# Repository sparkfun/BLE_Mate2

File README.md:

SparkFun BLE Mate 2
========================================

[*SparkFun BLE Mate 2 (WRL-13019)*](https://www.sparkfun.com/products/13019)

Repository Contents
-------------------

* **/Arduino** - All Arduino libraries and board examples
* **/Hardware** - All Eagle design files (.brd, .sch)
* **/Production** - Test bed files and production panel files

Version History
---------------
* [vH10L1.0.0](https://github.com/sparkfun/BLE_Mate2/tree/vH10L1.0.0) - Product version 10, library 1.0.0

License Information
-------------------
The hardware is released under [Creative Commons ShareAlike 4.0 International](https://creativecommons.org/licenses/by-sa/4.0/).
The code is beerware; if you see me (or any other SparkFun employee) at the local, and you've found our code helpful, please buy us a round!

Distributed as-is; no warranty is given.

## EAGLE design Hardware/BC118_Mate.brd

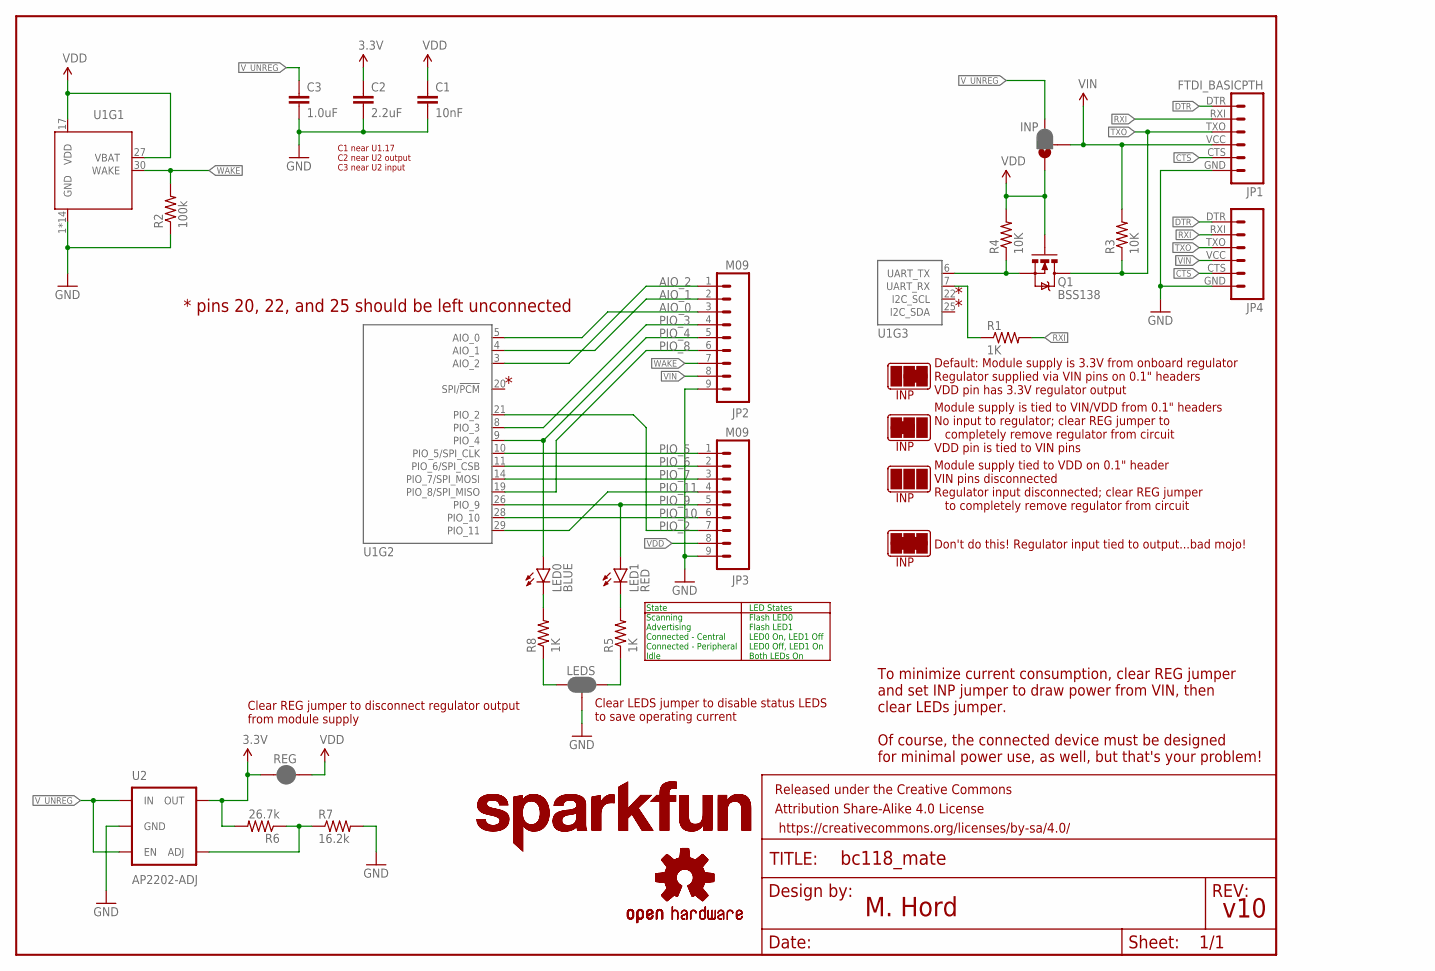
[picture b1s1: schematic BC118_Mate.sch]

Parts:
C1: 10nF; 0603-CAP
C2: 2.2uF; 0603-CAP
C3: 1.0uF; 0603-CAP
FRAME1: FRAME-LETTER; CREATIVE_COMMONS
INP: JUMPER-PAD-3-2OF3_NC_BY_PASTE; PAD-JUMPER-3-2OF3_NC_BY_PASTE_YES_SILK_FULL_BOX
JP1: FTDI_BASICPTH; FTDI_BASIC
JP2, JP3: M09; 1X09
JP4: M06SIP; 1X06
LED0: BLUE; LED-0603
LED1: RED; LED-0603
LEDS: JUMPER-PAD-3-NC_BY_PASTE; PAD-JUMPER-3-NC_BY_PASTE_YES_SILK_FULL_BOX
LOGO1, LOGO3: SFE_LOGO_NAME.1_INCH; SFE_LOGO_NAME_.1
LOGO2, LOGO4: OSHW-LOGOS; OSHW-LOGO-S
Q1: BSS138; SOT23
R1, R5, R8: 1K; 0603-RES
R2: 100k; 0603-RES
R3, R4: 10K; 0603-RES
R6: 26.7k; 0603-RES
R7: 16.2k; 0603-RES
REG: JUMPER-PAD-2-NC_BY_PASTE; PAD-JUMPER-2-NC_BY_PASTE_YES_SILK
U1: BC118
U2: AP2202-ADJ; SOT23-5

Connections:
3.3V: C2.1, R6.2, REG.1, U2.5 (OUT)
AIO_0: JP2.3, U1.5 (AIO_0)
AIO_1: JP2.2, U1.4 (AIO_1)
AIO_2: JP2.1, U1.3 (AIO_2)
CTS: JP1.CTS (5), JP4.CTS (5)
DTR: JP1.DTR (1), JP4.DTR (1)
GND: C1.2, C2.2, C3.2, JP1.GND (6), JP2.9, JP3.9, JP4.GND (6), LEDS.2, R2.1, R7.2, U1.1 (GND), U1.2 (GND), U1.12 (GND), U1.13 (GND), U1.15 (GND), U1.16 (GND), U1.18 (GND), U1.23 (GND), U1.24 (GND), U1.31 (GND), U1.32 (GND), U1.33 (GND), U1.34 (GND), U1.35 (GND), U2.2 (GND)
unnamed: R1.1, U1.7 (UART_RX)
unnamed: R6.1, R7.1, U2.4 (ADJ)
unnamed: Q1.2 (S), R4.1, U1.6 (UART_TX)
unnamed: LEDS.1, R8.1
unnamed: LEDS.3, R5.1
unnamed: LED0.C, R8.2
unnamed: LED1.C, R5.2
PIO_2: JP3.7, U1.21 (PIO_2)
PIO_3: JP2.4, U1.8 (PIO_3)
PIO_4: JP2.5, LED0.A, U1.9 (PIO_4)
PIO_5: JP3.1, U1.10 (PIO_5/SPI_CLK)
PIO_6: JP3.2, U1.11 (PIO_6/SPI_CSB)
PIO_7: JP3.3, U1.14 (PIO_7/SPI_MOSI)
PIO_8: JP2.6, U1.19 (PIO_8/SPI_MISO)
PIO_9: JP3.5, LED1.A, U1.26 (PIO_9)
PIO_10: JP3.6, U1.28 (PIO_10)
PIO_11: JP3.4, U1.29 (PIO_11)
RXI: JP1.RXI (2), JP4.RXI (2), R1.2
TXO: JP1.TXO (3), JP4.TXO (3), Q1.3 (D), R3.1
VDD: C1.1, INP.1, JP3.8, Q1.1 (G), R4.2, REG.2, U1.17 (VDD), U1.27 (VBAT)
VIN: INP.2, JP1.VCC (4), JP2.8, JP4.VCC (4), R3.2
V_UNREG: C3.1, INP.3, U2.1 (IN), U2.3 (EN)
WAKE: JP2.7, R2.2, U1.30 (WAKE)

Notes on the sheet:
State Scanning Advertising Connected - Central Connected - Peripheral Idle
LED States Flash LED0 Flash LED1 LED0 On, LED1 Off LED0 Off, LED1 On Both LEDs On
C1 near U1.17 C2 near U2 output C3 near U2 input
INP
Default: Module supply is 3.3V from onboard regulator Regulator supplied via VIN pins on 0.1" headers VDD pin has 3.3V regulator output
Module supply is tied to VIN/VDD from 0.1" headers No input to regulator; clear REG jumper to completely remove regulator from circuit VDD pin is tied to VIN pins
Module supply tied to VDD on 0.1" header VIN pins disconnected Regulator input disconnected; clear REG jumper to completely remove regulator from circuit
Don't do this! Regulator input tied to output...bad mojo!
Clear LEDS jumper to disable status LEDS to save operating current
Clear REG jumper to disconnect regulator output from module supply
* pins 20, 22, and 25 should be left unconnected
To minimize current consumption, clear REG jumper and set INP jumper to draw power from VIN, then clear LEDs jumper. Of course, the connected device must be designed for minimal power use, as well, but that's your problem!
M. Hord
v10

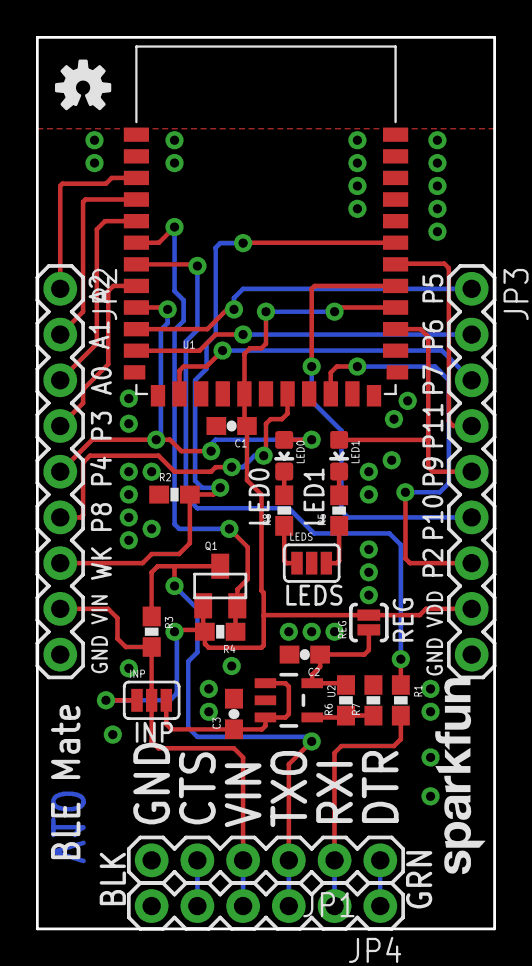
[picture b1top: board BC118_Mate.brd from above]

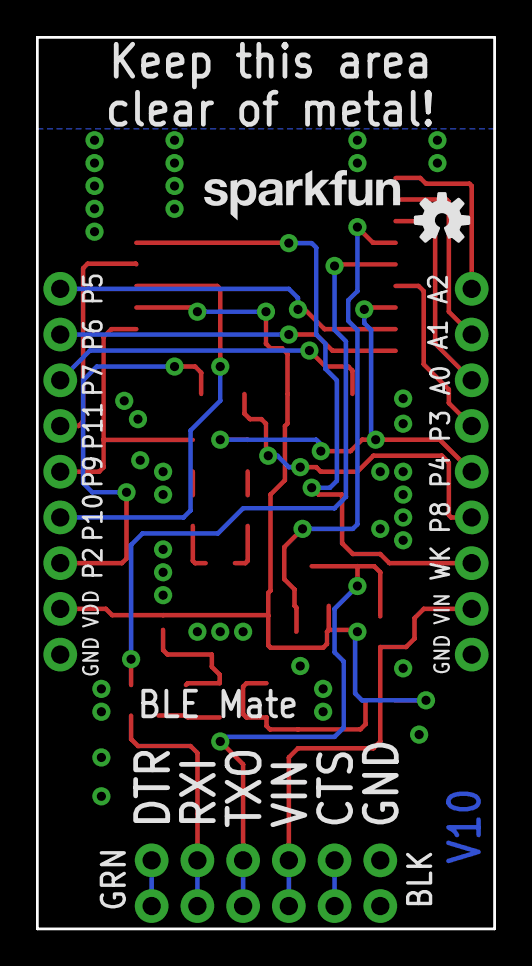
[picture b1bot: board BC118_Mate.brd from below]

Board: 2 copper layers, 25.4 x 49.5 mm, 28 parts (2 on the bottom side), 30 nets.

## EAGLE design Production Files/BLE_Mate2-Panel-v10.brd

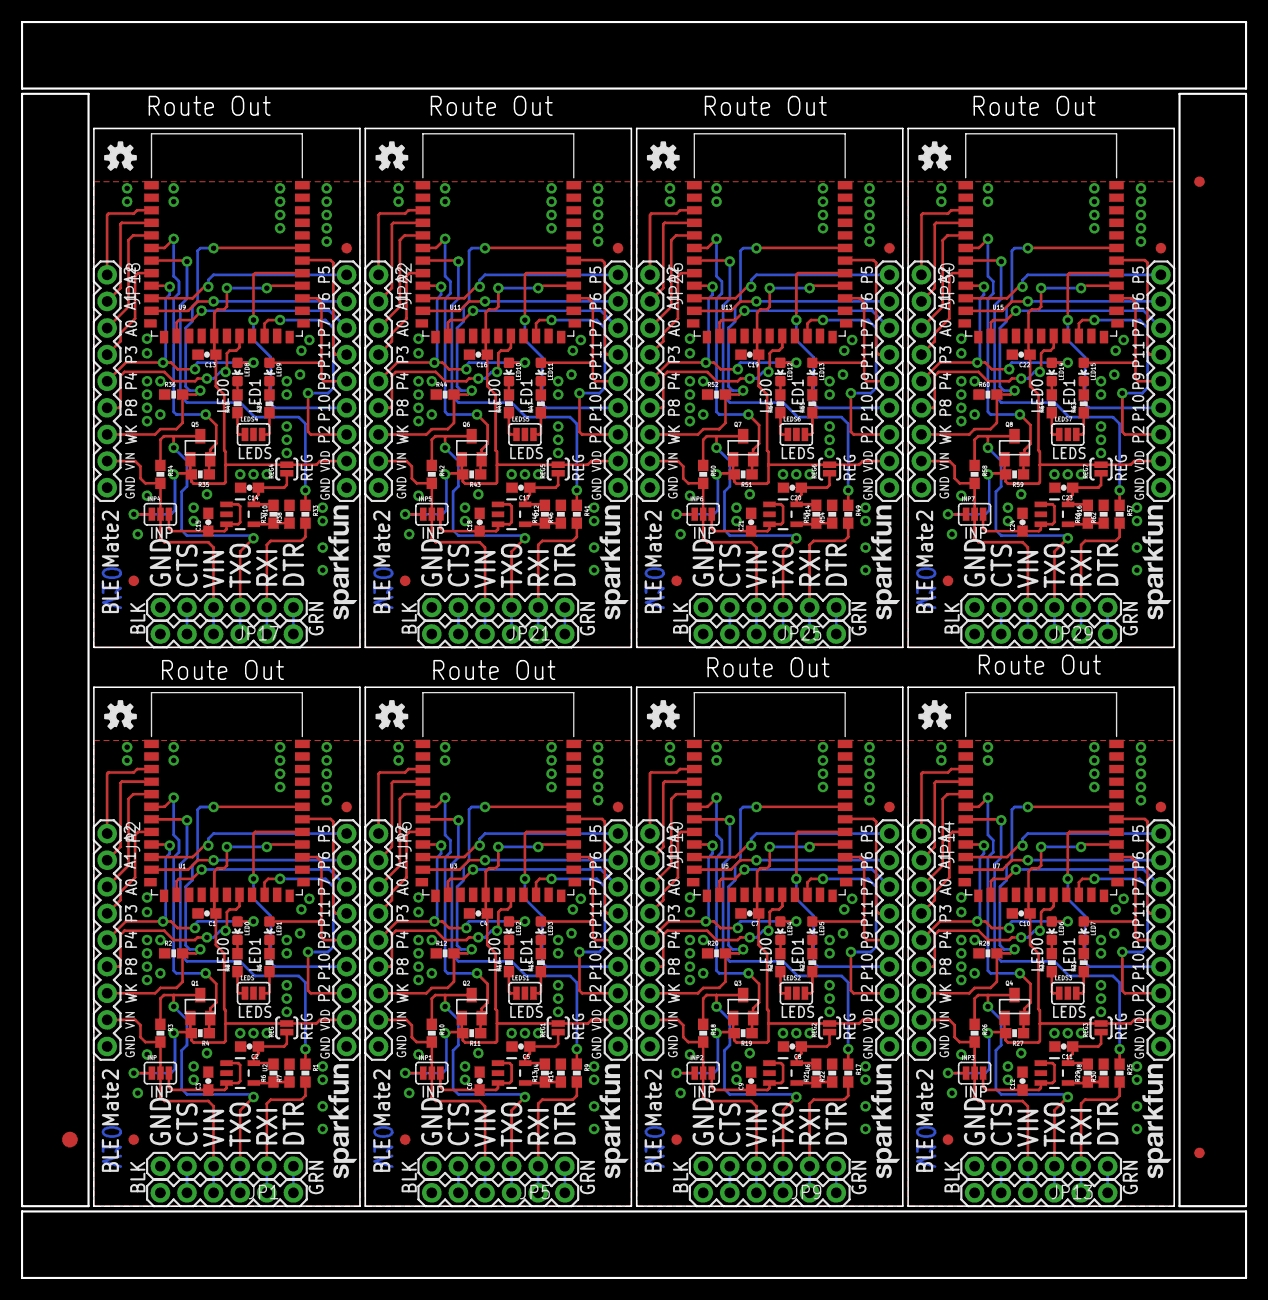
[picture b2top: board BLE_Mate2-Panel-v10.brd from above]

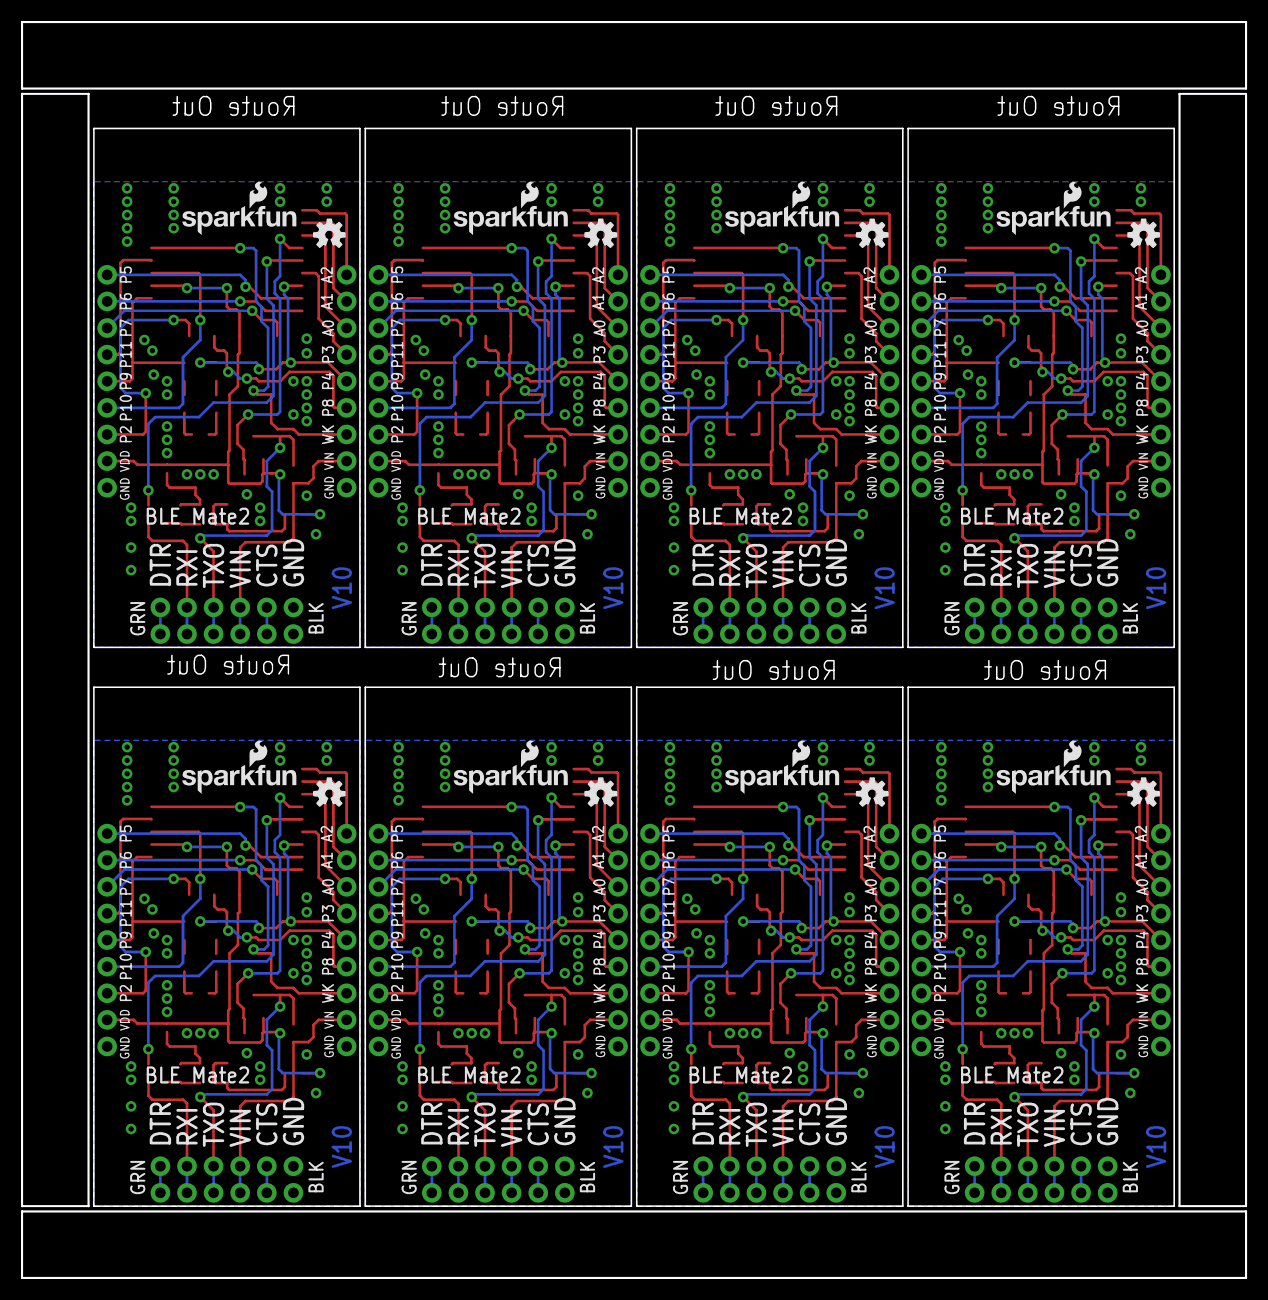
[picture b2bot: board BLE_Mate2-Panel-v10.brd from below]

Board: 2 copper layers, 116.8 x 119.9 mm, 235 parts (16 on the bottom side), 240 nets.

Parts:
C1, C4, C7, C10, C13, C16, C19, C22: 10nF; 0603-CAP
C2, C5, C8, C11, C14, C17, C20, C23: 2.2uF; 0603-CAP
C3, C6, C9, C12, C15, C18, C21, C24: 1.0uF; 0603-CAP
E$1: FIDUCIAL-1.5X3
E$4, E$5: FIDUCIAL-1X2
FID1, FID2, FID3, FID4, FID5, FID6, FID7, FID8, FID9, FID10, FID11, FID12, FID13, FID14, FID15, FID16: FIDUCIAL1X2; FIDUCIAL-1X2
INP, INP1, INP2, INP3, INP4, INP5, INP6, INP7: JUMPER-PAD-3-2OF3_NC_BY_PASTE; PAD-JUMPER-3-2OF3_NC_BY_PASTE_YES_SILK_FULL_BOX
JP1, JP5, JP9, JP13, JP17, JP21, JP25, JP29: FTDI_BASICPTH; FTDI_BASIC
JP2, JP3, JP6, JP7, JP10, JP11, JP14, JP15, JP18, JP19, JP22, JP23, JP26, JP27, JP30, JP31: M09; 1X09
JP4, JP8, JP12, JP16, JP20, JP24, JP28, JP32: 1X06
LED0, LED2, LED4, LED6, LED8, LED10, LED12, LED14: BLUE; LED-0603
LED1, LED3, LED5, LED7, LED9, LED11, LED13, LED15: RED; LED-0603
LEDS, LEDS1, LEDS2, LEDS3, LEDS4, LEDS5, LEDS6, LEDS7: JUMPER-PAD-3-NC_BY_PASTE; PAD-JUMPER-3-NC_BY_PASTE_YES_SILK_FULL_BOX
LOGO1, LOGO5, LOGO9, LOGO13, LOGO17, LOGO21, LOGO25, LOGO29: SFE_LOGO_NAME.1_INCH; SFE_LOGO_NAME_.1
LOGO2, LOGO4, LOGO6, LOGO8, LOGO10, LOGO12, LOGO14, LOGO16, LOGO18, LOGO20, LOGO22, LOGO24, LOGO26, LOGO28, LOGO30, LOGO32: OSHW-LOGOS; OSHW-LOGO-S
LOGO3, LOGO7, LOGO11, LOGO15, LOGO19, LOGO23, LOGO27, LOGO31: SFE_LOGO_NAME_FLAME.1_INCH; SFE_LOGO_NAME_FLAME_.1
Q1, Q2, Q3, Q4, Q5, Q6, Q7, Q8: BSS138; SOT23
R1, R5, R8, R9, R15, R16, R17, R23, R24, R25, R31, R32, R33, R39, R40, R41, R47, R48, R49, R55, R56, R57, R63, R64: 1K; 0603-RES
R2, R12, R20, R28, R36, R44, R52, R60: 100k; 0603-RES
R3, R4, R10, R11, R18, R19, R26, R27, R34, R35, R42, R43, R50, R51, R58, R59: 10K; 0603-RES
R6, R13, R21, R29, R37, R45, R53, R61: 16.2k; 0603-RES
R7, R14, R22, R30, R38, R46, R54, R62: 26.7k; 0603-RES
REG, REG1, REG2, REG3, REG4, REG5, REG6, REG7: JUMPER-PAD-2-NC_BY_PASTE; PAD-JUMPER-2-NC_BY_PASTE_YES_SILK
U1, U3, U5, U7, U9, U11, U13, U15: BC118
U2, U4, U6, U8, U10, U12, U14, U16: AP2202-ADJ; SOT23-5

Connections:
3.3V: C2.1, R6.2, REG.1, U2.5
3.3V1: C5.1, R13.2, REG1.1, U4.5
3.3V2: C8.1, R21.2, REG2.1, U6.5
3.3V3: C11.1, R29.2, REG3.1, U8.5
3.3V4: C14.1, R37.2, REG4.1, U10.5
3.3V5: C17.1, R45.2, REG5.1, U12.5
3.3V6: C20.1, R53.2, REG6.1, U14.5
3.3V7: C23.1, R61.2, REG7.1, U16.5
AIO_0: JP2.3, U1.5
AIO_1: JP2.2, U1.4
AIO_2: JP2.1, U1.3
AIO_3: JP6.1, U3.3
AIO_4: JP6.2, U3.4
AIO_5: JP6.3, U3.5
AIO_6: JP10.1, U5.3
AIO_7: JP10.2, U5.4
AIO_8: JP10.3, U5.5
AIO_9: JP14.1, U7.3
AIO_10: JP14.2, U7.4
AIO_11: JP14.3, U7.5
AIO_12: JP18.1, U9.3
AIO_13: JP18.2, U9.4
AIO_14: JP18.3, U9.5
AIO_15: JP22.1, U11.3
AIO_16: JP22.2, U11.4
AIO_17: JP22.3, U11.5
AIO_18: JP26.1, U13.3
AIO_19: JP26.2, U13.4
AIO_20: JP26.3, U13.5
AIO_21: JP30.1, U15.3
AIO_22: JP30.2, U15.4
AIO_23: JP30.3, U15.5
CTS: JP1.CTS, JP4.CTS
CTS1: JP5.CTS, JP8.CTS
CTS2: JP9.CTS, JP12.CTS
CTS3: JP13.CTS, JP16.CTS
CTS4: JP17.CTS, JP20.CTS
CTS5: JP21.CTS, JP24.CTS
CTS6: JP25.CTS, JP28.CTS
CTS7: JP29.CTS, JP32.CTS
DTR: JP1.DTR, JP4.DTR
DTR1: JP5.DTR, JP8.DTR
DTR2: JP9.DTR, JP12.DTR
DTR3: JP13.DTR, JP16.DTR
DTR4: JP17.DTR, JP20.DTR
DTR5: JP21.DTR, JP24.DTR
DTR6: JP25.DTR, JP28.DTR
DTR7: JP29.DTR, JP32.DTR
GND: C1.2, C2.2, C3.2, JP1.GND, JP2.9, JP3.9, JP4.GND, LEDS.2, R2.1, R7.2, U1.1, U1.2, U1.12, U1.13, U1.15, U1.16, U1.18, U1.23, U1.24, U1.31, U1.32, U1.33, U1.34, U1.35, U2.2
GND1: C4.2, C5.2, C6.2, JP5.GND, JP6.9, JP7.9, JP8.GND, LEDS1.2, R12.1, R14.2, U3.1, U3.2, U3.12, U3.13, U3.15, U3.16, U3.18, U3.23, U3.24, U3.31, U3.32, U3.33, U3.34, U3.35, U4.2
GND2: C7.2, C8.2, C9.2, JP9.GND, JP10.9, JP11.9, JP12.GND, LEDS2.2, R20.1, R22.2, U5.1, U5.2, U5.12, U5.13, U5.15, U5.16, U5.18, U5.23, U5.24, U5.31, U5.32, U5.33, U5.34, U5.35, U6.2
GND3: C10.2, C11.2, C12.2, JP13.GND, JP14.9, JP15.9, JP16.GND, LEDS3.2, R28.1, R30.2, U7.1, U7.2, U7.12, U7.13, U7.15, U7.16, U7.18, U7.23, U7.24, U7.31, U7.32, U7.33, U7.34, U7.35, U8.2
GND4: C13.2, C14.2, C15.2, JP17.GND, JP18.9, JP19.9, JP20.GND, LEDS4.2, R36.1, R38.2, U9.1, U9.2, U9.12, U9.13, U9.15, U9.16, U9.18, U9.23, U9.24, U9.31, U9.32, U9.33, U9.34, U9.35, U10.2
GND5: C16.2, C17.2, C18.2, JP21.GND, JP22.9, JP23.9, JP24.GND, LEDS5.2, R44.1, R46.2, U11.1, U11.2, U11.12, U11.13, U11.15, U11.16, U11.18, U11.23, U11.24, U11.31, U11.32, U11.33, U11.34, U11.35, U12.2
GND6: C19.2, C20.2, C21.2, JP25.GND, JP26.9, JP27.9, JP28.GND, LEDS6.2, R52.1, R54.2, U13.1, U13.2, U13.12, U13.13, U13.15, U13.16, U13.18, U13.23, U13.24, U13.31, U13.32, U13.33, U13.34, U13.35, U14.2
GND7: C22.2, C23.2, C24.2, JP29.GND, JP30.9, JP31.9, JP32.GND, LEDS7.2, R60.1, R62.2, U15.1, U15.2, U15.12, U15.13, U15.15, U15.16, U15.18, U15.23, U15.24, U15.31, U15.32, U15.33, U15.34, U15.35, U16.2
unnamed: R13.1, R14.1, U4.4
unnamed: R1.1, U1.7
unnamed: R6.1, R7.1, U2.4
unnamed: Q1.2, R4.1, U1.6
unnamed: LEDS.1, R8.1
unnamed: LEDS.3, R5.1
unnamed: Q2.2, R11.1, U3.6
unnamed: LED0.C, R8.2
unnamed: LED1.C, R5.2
unnamed: R9.1, U3.7
unnamed: LEDS1.1, R16.1
unnamed: LEDS1.3, R15.1
unnamed: LED2.C, R16.2
unnamed: LED3.C, R15.2
unnamed: R21.1, R22.1, U6.4
unnamed: Q3.2, R19.1, U5.6
unnamed: R17.1, U5.7
unnamed: LEDS2.1, R24.1
unnamed: LEDS2.3, R23.1
unnamed: LED4.C, R24.2
unnamed: LED5.C, R23.2
unnamed: R29.1, R30.1, U8.4
unnamed: Q4.2, R27.1, U7.6
unnamed: R25.1, U7.7
unnamed: LEDS3.1, R32.1
unnamed: LEDS3.3, R31.1
unnamed: LED6.C, R32.2
unnamed: LED7.C, R31.2
unnamed: R37.1, R38.1, U10.4
unnamed: Q5.2, R35.1, U9.6
unnamed: R33.1, U9.7
unnamed: LEDS4.1, R40.1
unnamed: LEDS4.3, R39.1
unnamed: LED8.C, R40.2
unnamed: LED9.C, R39.2
unnamed: R45.1, R46.1, U12.4
unnamed: Q6.2, R43.1, U11.6
unnamed: R41.1, U11.7
unnamed: LEDS5.1, R48.1
unnamed: LEDS5.3, R47.1
unnamed: LED10.C, R48.2
unnamed: LED11.C, R47.2
unnamed: R53.1, R54.1, U14.4
unnamed: Q7.2, R51.1, U13.6
unnamed: R49.1, U13.7
unnamed: LEDS6.1, R56.1
unnamed: LEDS6.3, R55.1
unnamed: LED12.C, R56.2
unnamed: LED13.C, R55.2
unnamed: R61.1, R62.1, U16.4
unnamed: Q8.2, R59.1, U15.6
unnamed: R57.1, U15.7
unnamed: LEDS7.1, R64.1
unnamed: LEDS7.3, R63.1
unnamed: LED14.C, R64.2
unnamed: LED15.C, R63.2
PIO_1: JP7.6, U3.28
PIO_2: JP3.7, U1.21
PIO_3: JP2.4, U1.8
PIO_4: JP2.5, LED0.A, U1.9
PIO_5: JP3.1, U1.10
PIO_6: JP3.2, U1.11
PIO_7: JP3.3, U1.14
PIO_8: JP2.6, U1.19
PIO_9: JP3.5, LED1.A, U1.26
PIO_10: JP3.6, U1.28
PIO_11: JP3.4, U1.29
PIO_12: JP7.5, LED3.A, U3.26
PIO_13: JP7.3, U3.14
PIO_14: JP7.2, U3.11
PIO_15: JP7.1, U3.10
PIO_16: JP6.5, LED2.A, U3.9
PIO_17: JP6.4, U3.8
PIO_18: JP7.7, U3.21
PIO_19: JP7.4, U3.29
PIO_20: JP6.6, U3.19
PIO_21: JP11.6, U5.28
PIO_22: JP11.5, LED5.A, U5.26
PIO_23: JP11.3, U5.14
PIO_24: JP11.2, U5.11
PIO_25: JP11.1, U5.10
PIO_26: JP10.5, LED4.A, U5.9
PIO_27: JP10.4, U5.8
PIO_28: JP11.7, U5.21
PIO_29: JP11.4, U5.29
PIO_30: JP10.6, U5.19
PIO_31: JP15.6, U7.28
PIO_32: JP15.5, LED7.A, U7.26
PIO_33: JP15.3, U7.14
PIO_34: JP15.2, U7.11
PIO_35: JP15.1, U7.10
PIO_36: JP14.5, LED6.A, U7.9
PIO_37: JP14.4, U7.8
PIO_38: JP15.7, U7.21
PIO_39: JP15.4, U7.29
PIO_40: JP14.6, U7.19
PIO_41: JP19.6, U9.28
PIO_42: JP19.5, LED9.A, U9.26
PIO_43: JP19.3, U9.14
PIO_44: JP19.2, U9.11
PIO_45: JP19.1, U9.10
PIO_46: JP18.5, LED8.A, U9.9
PIO_47: JP18.4, U9.8
PIO_48: JP19.7, U9.21
PIO_49: JP19.4, U9.29
PIO_50: JP18.6, U9.19
PIO_51: JP23.6, U11.28
PIO_52: JP23.5, LED11.A, U11.26
PIO_53: JP23.3, U11.14
PIO_54: JP23.2, U11.11
PIO_55: JP23.1, U11.10
PIO_56: JP22.5, LED10.A, U11.9
PIO_57: JP22.4, U11.8
PIO_58: JP23.7, U11.21
PIO_59: JP23.4, U11.29
PIO_60: JP22.6, U11.19
PIO_61: JP27.6, U13.28
PIO_62: JP27.5, LED13.A, U13.26
PIO_63: JP27.3, U13.14
PIO_64: JP27.2, U13.11
PIO_65: JP27.1, U13.10
PIO_66: JP26.5, LED12.A, U13.9
PIO_67: JP26.4, U13.8
PIO_68: JP27.7, U13.21
PIO_69: JP27.4, U13.29
PIO_70: JP26.6, U13.19
PIO_71: JP31.6, U15.28
PIO_72: JP31.5, LED15.A, U15.26
PIO_73: JP31.3, U15.14
PIO_74: JP31.2, U15.11
PIO_75: JP31.1, U15.10
PIO_76: JP30.5, LED14.A, U15.9
PIO_77: JP30.4, U15.8
PIO_78: JP31.7, U15.21
PIO_79: JP31.4, U15.29
PIO_80: JP30.6, U15.19
RXI: JP1.RXI, JP4.RXI, R1.2
RXI1: JP5.RXI, JP8.RXI, R9.2
RXI2: JP9.RXI, JP12.RXI, R17.2
RXI3: JP13.RXI, JP16.RXI, R25.2
RXI4: JP17.RXI, JP20.RXI, R33.2
RXI5: JP21.RXI, JP24.RXI, R41.2
RXI6: JP25.RXI, JP28.RXI, R49.2
RXI7: JP29.RXI, JP32.RXI, R57.2
TXO: JP1.TXO, JP4.TXO, Q1.3, R3.1
TXO1: JP5.TXO, JP8.TXO, Q2.3, R10.1
TXO2: JP9.TXO, JP12.TXO, Q3.3, R18.1
TXO3: JP13.TXO, JP16.TXO, Q4.3, R26.1
TXO4: JP17.TXO, JP20.TXO, Q5.3, R34.1
TXO5: JP21.TXO, JP24.TXO, Q6.3, R42.1
TXO6: JP25.TXO, JP28.TXO, Q7.3, R50.1
TXO7: JP29.TXO, JP32.TXO, Q8.3, R58.1
VDD: C1.1, INP.1, JP3.8, Q1.1, R4.2, REG.2, U1.17, U1.27
VDD1: C4.1, INP1.1, JP7.8, Q2.1, R11.2, REG1.2, U3.17, U3.27
VDD2: C7.1, INP2.1, JP11.8, Q3.1, R19.2, REG2.2, U5.17, U5.27
VDD3: C10.1, INP3.1, JP15.8, Q4.1, R27.2, REG3.2, U7.17, U7.27
VDD4: C13.1, INP4.1, JP19.8, Q5.1, R35.2, REG4.2, U9.17, U9.27
VDD5: C16.1, INP5.1, JP23.8, Q6.1, R43.2, REG5.2, U11.17, U11.27
VDD6: C19.1, INP6.1, JP27.8, Q7.1, R51.2, REG6.2, U13.17, U13.27
VDD7: C22.1, INP7.1, JP31.8, Q8.1, R59.2, REG7.2, U15.17, U15.27
VIN: INP.2, JP1.VCC, JP2.8, JP4.VCC, R3.2
VIN1: INP1.2, JP5.VCC, JP6.8, JP8.VCC, R10.2
VIN2: INP2.2, JP9.VCC, JP10.8, JP12.VCC, R18.2
VIN3: INP3.2, JP13.VCC, JP14.8, JP16.VCC, R26.2
VIN4: INP4.2, JP17.VCC, JP18.8, JP20.VCC, R34.2
VIN5: INP5.2, JP21.VCC, JP22.8, JP24.VCC, R42.2
VIN6: INP6.2, JP25.VCC, JP26.8, JP28.VCC, R50.2
VIN7: INP7.2, JP29.VCC, JP30.8, JP32.VCC, R58.2
V_UNREG: C3.1, INP.3, U2.1, U2.3
V_UNREG1: C6.1, INP1.3, U4.1, U4.3
V_UNREG2: C9.1, INP2.3, U6.1, U6.3
V_UNREG3: C12.1, INP3.3, U8.1, U8.3
V_UNREG4: C15.1, INP4.3, U10.1, U10.3
V_UNREG5: C18.1, INP5.3, U12.1, U12.3
V_UNREG6: C21.1, INP6.3, U14.1, U14.3
V_UNREG7: C24.1, INP7.3, U16.1, U16.3
WAKE: JP2.7, R2.2, U1.30
WAKE1: JP6.7, R12.2, U3.30
WAKE2: JP10.7, R20.2, U5.30
WAKE3: JP14.7, R28.2, U7.30
WAKE4: JP18.7, R36.2, U9.30
WAKE5: JP22.7, R44.2, U11.30
WAKE6: JP26.7, R52.2, U13.30
WAKE7: JP30.7, R60.2, U15.30

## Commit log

2014-07-07 Initial commit.
2014-07-14 V01 ready for protos
2014-07-15 Update BC118 with part info
2014-10-07 Change LED pin assignments to match new firmware
2014-10-27 Ready for reds
2014-10-27 Rename hardware files
2014-10-27 added board fiducials
2014-10-29 created panel v10
2014-11-21 Add example code, library.
2014-11-21 Rename/restructure files to SFE standards
2015-01-15 Adding product info to README
2015-05-05 Renamed, restructured files
2015-05-05 Squashed 'Libraries/Arduino/' content from commit 2ead2d9
    git-subtree-dir: Libraries/Arduino
    git-subtree-split: 2ead2d9625ff02445bcaa97c111b7e216bf73175
2015-05-05 Added library in

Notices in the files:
parts and their libraries:
SparkFun-Aesthetics: Licensing: Creative Commons ShareAlike 4.0 International - https://creativecommons.org/licenses/by-sa/4.0
SparkFun-Aesthetics: Released under the Creative Commons Attribution Share-Alike 4.0 License
SparkFun-Aesthetics: Released under the Creative Commons
